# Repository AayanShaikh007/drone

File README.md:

# Multicopter

## Goal: 
_To design a polished multipurpose drone that can carry various payloads._

## Requirements:
- Needs to have a polished appearance (plastic shell with lights, speakers) (difficult)
- Solid attachment points for payloads (difficult, see 1.) - Will require pcb design. 
- Attachment types: String based attachment, Package release mechanism. 
- Gimbal to carry thermal OR regular camera. (easy, Probably going to buy this and attach it, too complicated to make)

## Drone parameters:
Size: Medium (250-400 mm) or Large (400+ mm)

## Supplies:
- Going to need a flight controller that can operate over CAN bus (around 100 dollars)
- I like this flight controller: Pixhawk 6C Mini Model A – DroneDynamics.ca
- GNSS
- Already have PETG for printing the frame.

My interest in drones sparked when i was in Grade 4, when I saw an individual using a DJI Phantom to perform photography at a welcoming parade in Toronto. Ever since then, I was intrigued by drones and their numerous applications. Nowadays, I find it annoying that companies such as DJI are commercializing their drones, designing them to perform one purpose or task (photography, FPV, search and rescue, agriculture, etc). I agree that it is difficult or unrealistic to make a drone that can do everything, but there are some merits to it. For example, drones should at least be such that they can be used for FPV flying as well as casual photography, so that consumer waste can be reduced. 

In larger cities, road traffic is becoming a major issue. Not only is it greatly contributing to climate change, it also affects everyone who depends on the city by afflicting them with stress and potentially even physical harm (vehicle accidents). Due to this, I aim to prototype a delivery drone that could eventually be scaled up to perform deliveries of day to day essentials. 

WIth that said, I plan to make a multipurpose autonomous drone, maybe with some components I have. 

Goals
- Return to home (easy)
- Obstacle avoidance
- Auto fly and follow (hard)
- Autonomous address package delivery (special) 
- Add a mode where it goes to a set height, goes to the specific coordinates where the recipient has stated clear skies, and land. 
- For this, something resembling a DJI Dock will be required.

I officially began this project (research) today, on June 15th. I spent around 3-4 hours researching components of the drone and what I will need to buy to create the drone. Since this project will be very heavily CAD based, it will be a very good learning opportunity as well since I will be able to learn alot about CAD analysis and producing functional prints. 

# Project Gallery

# BOM

| Item                   | Amount | Bought? | Cost (CAD) | Total Cost | Notes              | Link |
|------------------------|--------|---------|------------|------------|--------------------|------|
| Motors                 | 4      | n       | 17.38      | 69.52      |                    | [Link](https://www.aliexpress.com/item/1005007351717901.html?spm=a2g0o.productlist.main.1.1a32ZabUZabUfY) |
| ESC                   | 4      | n       | 6.3        | 25.2       |                    | [Link](https://www.aliexpress.com/item/1005007431507565.html?spm=a2g0o.productlist.main.1.79a3hJznhJznry) |
| Battery               | 1      | n       | 145.38     | 145.38     | (includes 2)       | [Link](https://www.aliexpress.com/item/1005004995261155.html?spm=a2g0o.productlist.main.1.60c439e7z7KGuy) |
| Radiolink FC          | 1      | n       | 31.18      | 31.18      |                    | [Link](https://www.aliexpress.com/item/1005009514369066.html?spm=a2g0o.productlist.main.11.72146403dDdVeX) |
| Power Dist. Board     | 1      | n       | 10.48      | 10.48      |                    | [Link](https://www.aliexpress.com/item/1005007472949326.html?spm=a2g0o.productlist.main.3.10b24310suD8nY) |
| Controller            | 1      | n       | 107.99     | 107.99     |                    | [Link](https://www.amazon.ca/Radiolink-T12D-Transmitter-Telemetry-Long-Range/dp/B0DB5JHSS6) |
| Propellors            | 1      | n       | 15.58      | 15.58      | includes 4 obviously | [Link](https://www.aliexpress.com/item/1005007471007910.html?spm=a2g0o.productlist.main.4.1ee12b0817sXsu) |
| M5x20 Screws          | 1      | n       | 5.2        | 5.2        |                    | [Link](https://www.aliexpress.com/item/1005004801296825.html?spm=a2g0o.productlist.main.1.5d541488qCS2BO) |
| M3x10 Screws          | 1      | n       | 4.34       | 4.34       | includes 10        | [Link](https://www.aliexpress.com/item/1005007360894545.html?spm=a2g0o.productlist.main.1.f39e5ce9wdB1FY) |
| Velcro Straps         | 8      | y       | 0          | 0          | already owned      |      |
| Double Sided Tape     | 1      | y       | 0          | 0          | already owned      |      |

|                      |        |         | CAD        | USD        |                    |
|----------------------|--------|---------|------------|------------|--------------------|
|                      |        | Total Cost | **414.87** | **299.41** |                    |
|                      |        |         |            |            | Note: 150 USD = 204.58 CAD |

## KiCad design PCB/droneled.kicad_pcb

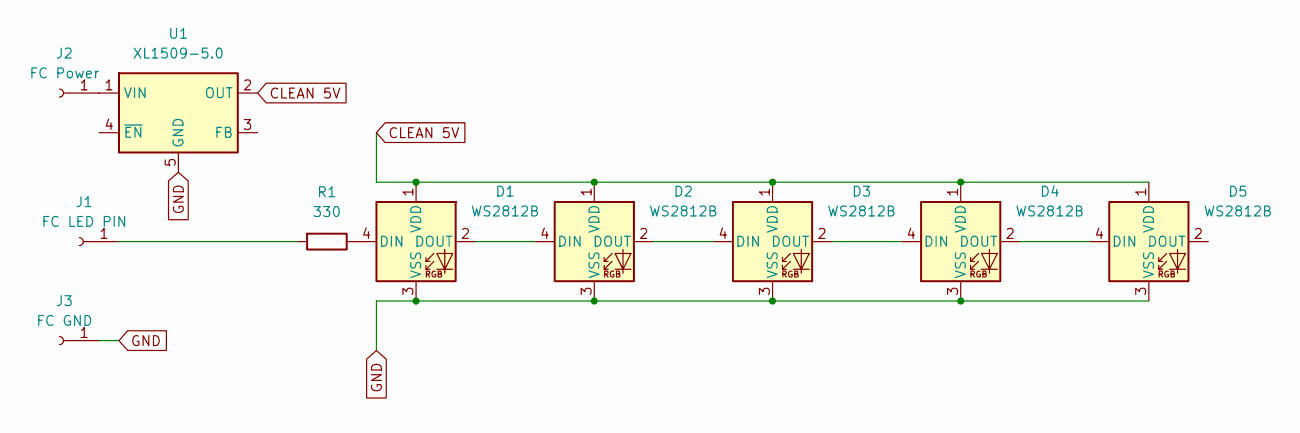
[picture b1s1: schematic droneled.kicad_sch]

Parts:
D1, D2, D3, D4, D5: WS2812B; BAcklight
J1: FC LED PIN; PinHeader_1x01_P2.54mm_Vertical
J2: FC Power; PinHeader_1x01_P2.54mm_Vertical
J3: FC GND; PinHeader_1x01_P2.54mm_Vertical
R1: 330; R_Axial_DIN0204_L3.6mm_D1.6mm_P5.08mm_Vertical
U1: XL1509-5.0; SOIC-8_3.9x4.9mm_P1.27mm

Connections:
CLEAN 5V: D1.1 (VDD), D2.1 (VDD), D3.1 (VDD), D4.1 (VDD), D5.1 (VDD), U1.2 (OUT)
GND: D1.3 (VSS), D2.3 (VSS), D3.3 (VSS), D4.3 (VSS), D5.3 (VSS), J3.1, U1.5 (GND), U1.6 (GND), U1.7 (GND), U1.8 (GND)
unnamed: D1.4 (DIN), R1.1
unnamed: D1.2 (DOUT), D2.4 (DIN)
unnamed: D2.2 (DOUT), D3.4 (DIN)
unnamed: D3.2 (DOUT), D4.4 (DIN)
unnamed: D4.2 (DOUT), D5.4 (DIN)
unnamed: J1.1, R1.2
unnamed: J2.1, U1.1 (VIN)

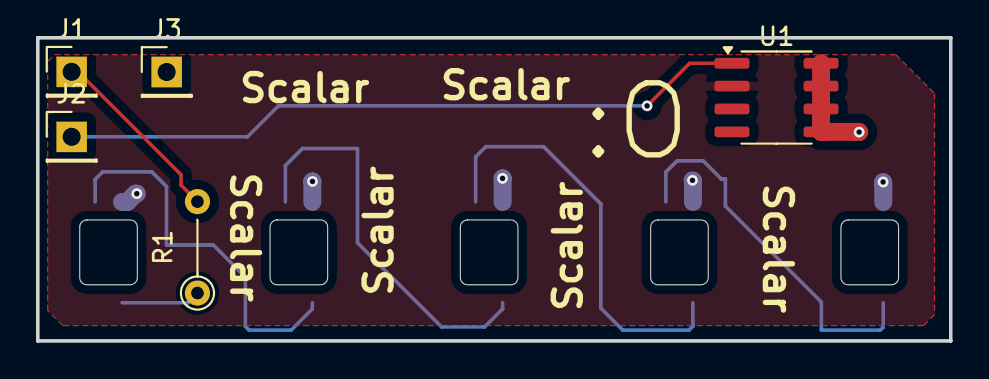
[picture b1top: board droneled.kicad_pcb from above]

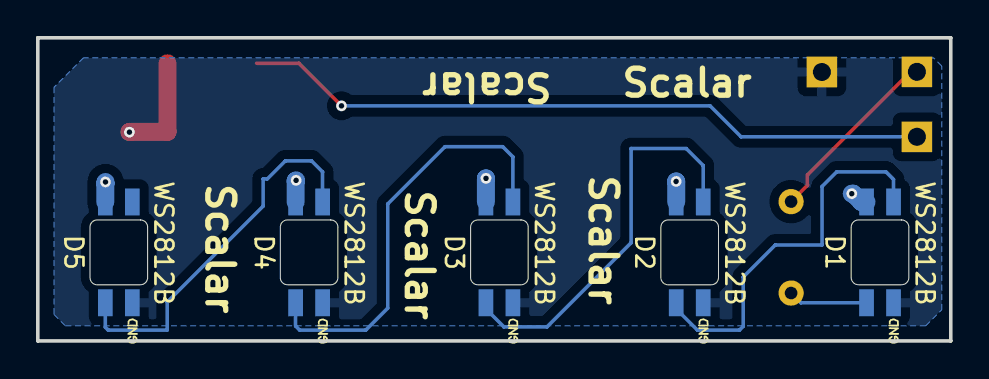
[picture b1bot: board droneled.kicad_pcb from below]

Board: 2 copper layers, 50.7 x 16.8 mm, 10 parts (5 on the bottom side), 9 nets.

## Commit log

2025-08-04 adding 3d models of components
2025-08-16 more cad
